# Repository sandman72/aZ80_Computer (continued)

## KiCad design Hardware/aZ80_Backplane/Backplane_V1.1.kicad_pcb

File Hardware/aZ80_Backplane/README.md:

# aZ80 Bus-Platine

Die Bus-Platine bildet das Rückgrat unseres Computers. Sie verbindet die einzelnen Karten des aZ80 miteinander.

Die sieben Slots sind alle gleich belegt und leiten den Adress- und Datenbus sowie die Kontrollsignale und die Versorgungsspannung weiter an die verschiedenen Karten.

Die LED D2 zeigt an, dass eine Versorgungsspannung anliegt.

Der Taster SW1 erlaubt das Zurücksetzen und Neustarten des Computers, der sogenannte RESET. Dies ist hilfreich, wenn der aZ80 mal nicht mehr reagieren sollte.

Im Kurs zeigen wir euch, wie man diese Platinen am besten zusammen lötet.

#### Externe Anschlüsse:

 - J1 - Steckleiste für Serielles Interfaces (FTDI Belegung)
 - J2 - Buchse für die externe 5V Versorgungsspannung (Barrel-Jack, Mitte +5V)
 - J3 - +5V Messpunkt für die Versorgungsspannung.
 - J4 - Masse Messpunkt für die Versorgungsspannung.

#### Steckbrücken (Jumper):

 - JP1 - Steuerleitung RTS des FTDI USB Seriell Wandlers mit Leitung USR1 verbinden
 - JP2 - Stromversorgung per FTDI USB Seriell Wandler erlauben

Unser aZ80 Computer benötigt eine +5V Versorgungsspannung von etwa 300mA, was einen Betrieb über den FTDI USB Seriell Wandler erlaubt, wenn nicht noch weitere Zusatzkarten (Video, Audio usw.) eingesteckt sind. In diesem Falle sollte man über die Buchse J2 ein USB-Netzteil anschließen.

Der BUS ist größtenteils kompatibel mit dem sogenannten RC40 System (Retro Computer 40), dass auch im RC2014 Computer benutzt wird. Hierzu gibt es diverse Erweiterungsplatinen, die auch zum großen Teil mit dem aZ80 kompatibel sind.

#### Pin-Belegung der aZ80 Busses:

|   Pin   |  Signal  |
|--------:|:---------|
|  1 - 16 | A15-A0 	Adress-Bus | 
|      17 | GND		Masse |
|      18 | VCC +5V	Versorgungsspannung |
|      19 | M1		Steuerungssignal |
|      20 | RESET		Zurücksetzen des Systems |
|      21 | CLOCK		Taktsignal 3,68MHz |
|      22 | INT		Interrupt, Unterbrechungsanforderung |
|      23 | MREQ		Memory Request, Speicheranfrage |
|      24 | WR		Write, Daten schreiben |
|      25 | RD		Read, Daten lesen |
|      26 | IORQ		I/O Request, I/O-Anfrage |
| 27 - 34 | D0-D7		Daten-Bus |
|      35 | TX		Serielle Daten Senden |
|      36 | RX		Serielle Daten Empfangen |
| 37 - 40 | USR1-USR4	Benutzerdefinierte Signale |  

Der Adress- und Daten-Bus ermöglicht dem Prozessor/CPU mit den einzelnen Karten Daten auszutauschen. Dabei enthält der Adress-Bus, wenn man so will, die Adresse eines Postfachs in das man was reinlegen oder rausholen möchte. Der Daten-Bus enthält die Information die dort gelesen wurde oder abgelegt werden soll.

Mit den Steuersignale (RD, WR, MREQ, IORQ, M1) legt der Prozessor fest, wie und von wo etwas gelesen oder geschrieben werden soll.   

#### Benutzerdefinierte Signale USR1-USR4:

Die vier USR1-USR4 Pins kann man selber nach Bedarf belegen. Die Serielle Karte kann z.B. über die Steuerleitung USR1 mit dem FTDI Seriell Wandler verbunden werden, was eine Flusssteuerung der Daten erlaubt. Dies ist nötig, wenn unser aZ80 lange BASIC Programme empfangen und nichts verloren gehen soll.

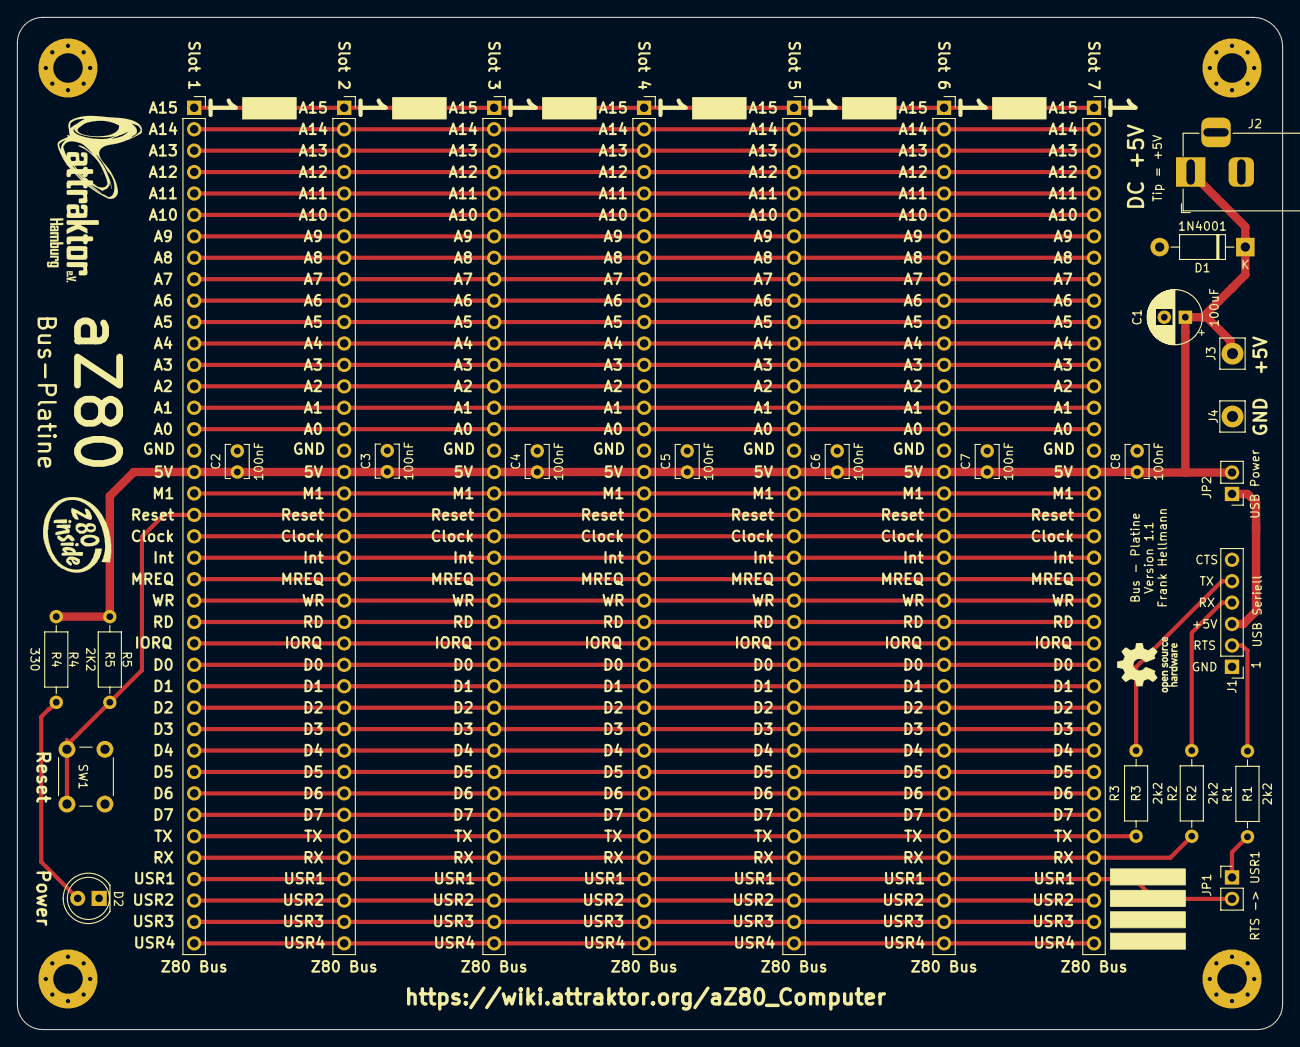
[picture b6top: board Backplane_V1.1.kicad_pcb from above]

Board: 2 copper layers, 150.0 x 120.0 mm, 33 parts (0 on the bottom side), 46 nets.

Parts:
C1: 100uF; CP_Radial_D6.3mm_P2.50mm
C2, C3, C4, C5, C6, C7, C8: 100nF; C_Disc_D3.8mm_W2.6mm_P2.50mm
D1: 1N4001; D_DO-41_SOD81_P10.16mm_Horizontal
D2: Power; LED_D5.0mm
Hole1, Hole2, Hole3, Hole4: MountingHole_3.5mm_Pad_Via
J1: USB Seriell; PinHeader_1x06_P2.54mm_Vertical
J2: DC +5V; BarrelJack_Horizontal
J3: +5V Hook; Pin_D1.3mm_L10.0mm_W3.5mm_Flat
J4: GND Hook; Pin_D1.3mm_L10.0mm_W3.5mm_Flat
JP1: RTS -> USR1; PinHeader_1x02_P2.54mm_Vertical
JP2: 5V USB; PinHeader_1x02_P2.54mm_Vertical
R1, R2, R3: 2k2; R_Axial_DIN0207_L6.3mm_D2.5mm_P10.16mm_Horizontal
R4: 330; R_Axial_DIN0207_L6.3mm_D2.5mm_P10.16mm_Horizontal
R5: 2K2; R_Axial_DIN0207_L6.3mm_D2.5mm_P10.16mm_Horizontal
SW1: Reset; SW_PUSH_6mm
Slot 1, Slot 2, Slot 3, Slot 4, Slot 5, Slot 6, Slot 7: Z80 Bus; PinSocket_1x40_P2.54mm_Vertical

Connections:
5V: C1.1, C2.1, C3.1, C4.1, C5.1, C6.1, C7.1, C8.1, D1.1, J2.1, J3.1, JP2.2, R4.1, R5.2, Slot 1.18, Slot 2.18, Slot 3.18, Slot 4.18, Slot 5.18, Slot 6.18, Slot 7.18
/A0: Slot 1.16, Slot 2.16, Slot 3.16, Slot 4.16, Slot 5.16, Slot 6.16, Slot 7.16
/A1: Slot 1.15, Slot 2.15, Slot 3.15, Slot 4.15, Slot 5.15, Slot 6.15, Slot 7.15
/A2: Slot 1.14, Slot 2.14, Slot 3.14, Slot 4.14, Slot 5.14, Slot 6.14, Slot 7.14
/A3: Slot 1.13, Slot 2.13, Slot 3.13, Slot 4.13, Slot 5.13, Slot 6.13, Slot 7.13
/A4: Slot 1.12, Slot 2.12, Slot 3.12, Slot 4.12, Slot 5.12, Slot 6.12, Slot 7.12
/A5: Slot 1.11, Slot 2.11, Slot 3.11, Slot 4.11, Slot 5.11, Slot 6.11, Slot 7.11
/A6: Slot 1.10, Slot 2.10, Slot 3.10, Slot 4.10, Slot 5.10, Slot 6.10, Slot 7.10
/A7: Slot 1.9, Slot 2.9, Slot 3.9, Slot 4.9, Slot 5.9, Slot 6.9, Slot 7.9
/A8: Slot 1.8, Slot 2.8, Slot 3.8, Slot 4.8, Slot 5.8, Slot 6.8, Slot 7.8
/A9: Slot 1.7, Slot 2.7, Slot 3.7, Slot 4.7, Slot 5.7, Slot 6.7, Slot 7.7
/A10: Slot 1.6, Slot 2.6, Slot 3.6, Slot 4.6, Slot 5.6, Slot 6.6, Slot 7.6
/A11: Slot 1.5, Slot 2.5, Slot 3.5, Slot 4.5, Slot 5.5, Slot 6.5, Slot 7.5
/A12: Slot 1.4, Slot 2.4, Slot 3.4, Slot 4.4, Slot 5.4, Slot 6.4, Slot 7.4
/A13: Slot 1.3, Slot 2.3, Slot 3.3, Slot 4.3, Slot 5.3, Slot 6.3, Slot 7.3
/A14: Slot 1.2, Slot 2.2, Slot 3.2, Slot 4.2, Slot 5.2, Slot 6.2, Slot 7.2
/A15: Slot 1.1, Slot 2.1, Slot 3.1, Slot 4.1, Slot 5.1, Slot 6.1, Slot 7.1
/CLK: Slot 1.21, Slot 2.21, Slot 3.21, Slot 4.21, Slot 5.21, Slot 6.21, Slot 7.21
/D0: Slot 1.27, Slot 2.27, Slot 3.27, Slot 4.27, Slot 5.27, Slot 6.27, Slot 7.27
/D1: Slot 1.28, Slot 2.28, Slot 3.28, Slot 4.28, Slot 5.28, Slot 6.28, Slot 7.28
/D2: Slot 1.29, Slot 2.29, Slot 3.29, Slot 4.29, Slot 5.29, Slot 6.29, Slot 7.29
/D3: Slot 1.30, Slot 2.30, Slot 3.30, Slot 4.30, Slot 5.30, Slot 6.30, Slot 7.30
/D4: Slot 1.31, Slot 2.31, Slot 3.31, Slot 4.31, Slot 5.31, Slot 6.31, Slot 7.31
/D5: Slot 1.32, Slot 2.32, Slot 3.32, Slot 4.32, Slot 5.32, Slot 6.32, Slot 7.32
/D6: Slot 1.33, Slot 2.33, Slot 3.33, Slot 4.33, Slot 5.33, Slot 6.33, Slot 7.33
/D7: Slot 1.34, Slot 2.34, Slot 3.34, Slot 4.34, Slot 5.34, Slot 6.34, Slot 7.34
/INT: Slot 1.22, Slot 2.22, Slot 3.22, Slot 4.22, Slot 5.22, Slot 6.22, Slot 7.22
/IORQ: Slot 1.26, Slot 2.26, Slot 3.26, Slot 4.26, Slot 5.26, Slot 6.26, Slot 7.26
/M1: Slot 1.19, Slot 2.19, Slot 3.19, Slot 4.19, Slot 5.19, Slot 6.19, Slot 7.19
/MREQ: Slot 1.23, Slot 2.23, Slot 3.23, Slot 4.23, Slot 5.23, Slot 6.23, Slot 7.23
/RD: Slot 1.25, Slot 2.25, Slot 3.25, Slot 4.25, Slot 5.25, Slot 6.25, Slot 7.25
/WR: Slot 1.24, Slot 2.24, Slot 3.24, Slot 4.24, Slot 5.24, Slot 6.24, Slot 7.24
GND: C1.2, C2.2, C3.2, C4.2, C5.2, C6.2, C7.2, C8.2, D1.2, D2.1, J1.1, J2.2, J4.1, SW1.2, Slot 1.17, Slot 2.17, Slot 3.17, Slot 4.17, Slot 5.17, Slot 6.17, Slot 7.17
unnamed: D2.2, R4.2
unnamed: J1.2, R1.2
unnamed: J1.3, JP2.1
unnamed: J1.4, R2.2
unnamed: J1.5, R3.2
unnamed: JP1.1, R1.1
RX: R2.1, Slot 1.36, Slot 2.36, Slot 3.36, Slot 4.36, Slot 5.36, Slot 6.36, Slot 7.36
Reset: R5.1, SW1.1, Slot 1.20, Slot 2.20, Slot 3.20, Slot 4.20, Slot 5.20, Slot 6.20, Slot 7.20
TX: R3.1, Slot 1.35, Slot 2.35, Slot 3.35, Slot 4.35, Slot 5.35, Slot 6.35, Slot 7.35
USR1: JP1.2, Slot 1.37, Slot 2.37, Slot 3.37, Slot 4.37, Slot 5.37, Slot 6.37, Slot 7.37
USR2: Slot 1.38, Slot 2.38, Slot 3.38, Slot 4.38, Slot 5.38, Slot 6.38, Slot 7.38
USR3: Slot 1.39, Slot 2.39, Slot 3.39, Slot 4.39, Slot 5.39, Slot 6.39, Slot 7.39
USR4: Slot 1.40, Slot 2.40, Slot 3.40, Slot 4.40, Slot 5.40, Slot 6.40, Slot 7.40

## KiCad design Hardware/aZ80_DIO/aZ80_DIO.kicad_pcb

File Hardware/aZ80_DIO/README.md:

# aZ80 Digital I/O Platine

Die DIO (Digital I/O) Platine stellt über Taster, Joystick Anschluss und LEDs eine Verbindung zur Aussenwelt her.

#### Port Auswahl

Über den Jumperblock JP1 kann die Adresse (Port) eingestellt werden, auf den die DIO Platine reagieren soll. 
Normalerweise ist dort O0 und I0 gesteckt, was bedeutet, dass die DIO Platine auf Addresse 0 beim Lesen und Schreiben reagiert.
Damit können auch mehrere Karten in einem aZ80 System genutzt werden, wenn alle Karten unterschiedliche Addressen bekommen.

#### LEDs

Die LEDs können über die eingestellte Addresse mit einem I/O Write eingeschaltet werden. 

```
Basic:   OUT 0, 170             schaltet jede zweite LED an Port 0 an.

ASM:     LD      A,%10101010
         OUT     IOPORT,A       schaltet jede zweite LED an Port 0 an.
```

#### Taster & Joystick

Die Taster und der Joystick können über die eingestellte Addresse mit einem I/O Read ausgelesen werden.

```
Basic:   A$=INP(0)     liest den Status der Taster in A$ ein

ASM:     IN A,(0)      liest den Status der Taster in Register A
```

#### Basic Beispiel um LED mit Button einzuschalten

```
10 OUT 0,INP(0)
20 GOTO 10
```

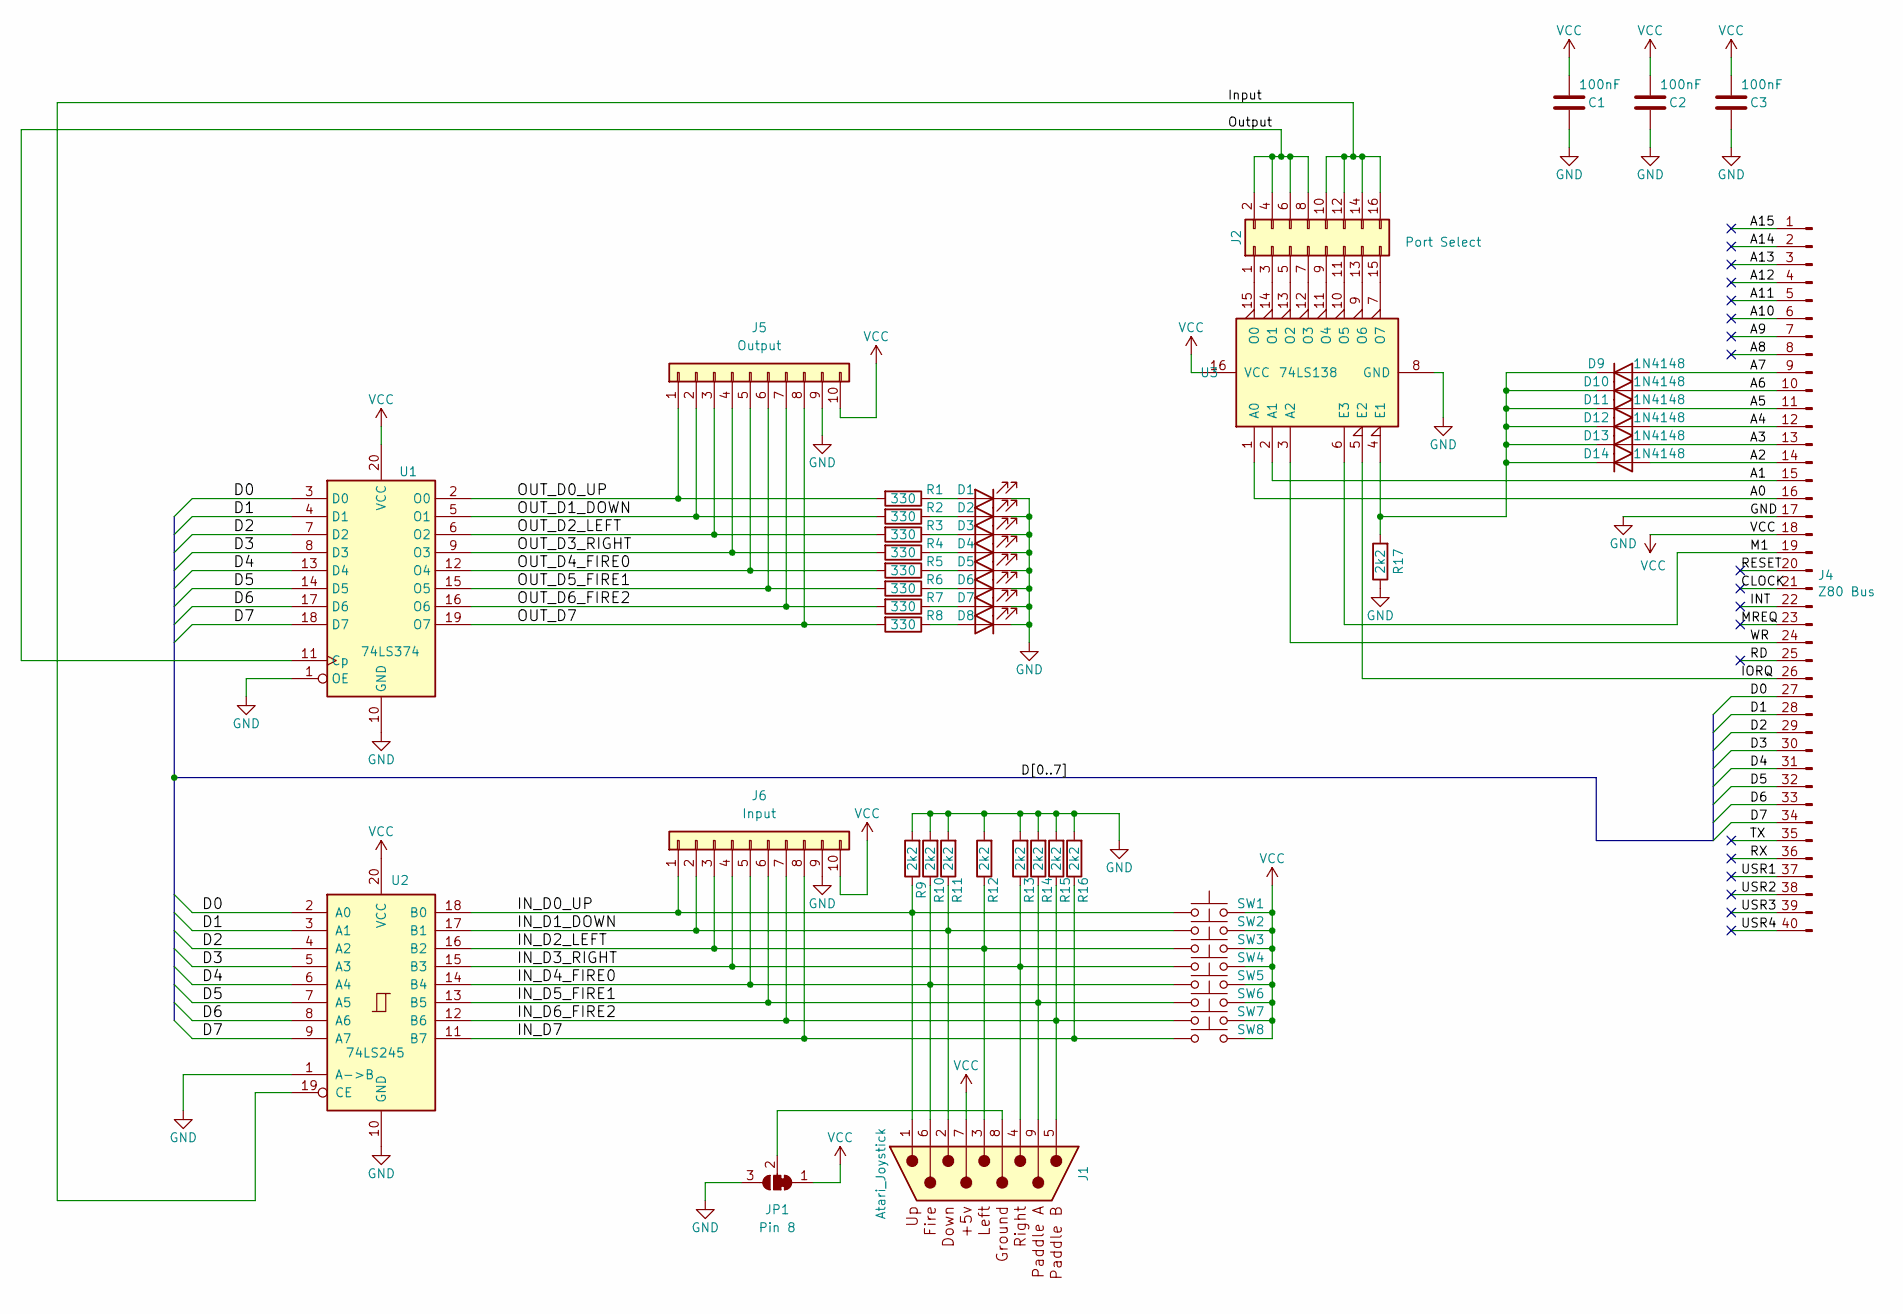
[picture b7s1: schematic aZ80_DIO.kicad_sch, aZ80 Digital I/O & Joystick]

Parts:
C1, C2, C3: 100nF; C_Disc_D3.8mm_W2.6mm_P2.50mm
D1, D2, D3, D4, D5, D6, D7, D8: LED_Small; LED_D5.0mm
D9, D10, D11, D12, D13, D14: 1N4148; D_DO-35_SOD27_P7.62mm_Horizontal
J1: Atari_Joystick; DSUB-9_Male_Horizontal_P2.77x2.84mm_EdgePinOffset7.70mm_Hou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
J2: Port Select; PinHeader_2x08_P2.54mm_Vertical
J4: Z80 Bus; PinHeader_1x40_P2.54mm_Horizontal
J5: Output; PinHeader_1x10_P2.54mm_Vertical
J6: Input; PinHeader_1x10_P2.54mm_Vertical
JP1: Pin 8; SolderJumper-3_P1.3mm_Bridged2Bar12_RoundedPad1.0x1.5mm
R1, R2, R3, R4, R5, R6, R7, R8: 330; R_Axial_DIN0207_L6.3mm_D2.5mm_P10.16mm_Horizontal
R9, R10, R11, R12, R13, R14, R15, R16, R17: 2k2; R_Axial_DIN0207_L6.3mm_D2.5mm_P10.16mm_Horizontal
SW1, SW2, SW3, SW4, SW5, SW6, SW7, SW8: SW_Push; SW_PUSH_6mm
U1: 74LS374; DIP-20_W7.62mm_LongPads
U2: 74LS245; DIP-20_W7.62mm_LongPads
U3: 74LS138; DIP-16_W7.62mm_LongPads

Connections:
/A0: J4.16, U3.1 (A0)
/A1: J4.15, U3.2 (A1)
/A2: D14.2 (A), J4.14
/A3: D13.2 (A), J4.13
/A4: D12.2 (A), J4.12
/A5: D11.2 (A), J4.11
/A6: D10.2 (A), J4.10
/A7: D9.2 (A), J4.9
/A8: J4.8
/A9: J4.7
/A10: J4.6
/A11: J4.5
/A12: J4.4
/A13: J4.3
/A14: J4.2
/A15: J4.1
/CLOCK: J4.21
/D0: J4.27, U1.3 (D0), U2.2 (A0)
/D1: J4.28, U1.4 (D1), U2.3 (A1)
/D2: J4.29, U1.7 (D2), U2.4 (A2)
/D3: J4.30, U1.8 (D3), U2.5 (A3)
/D4: J4.31, U1.13 (D4), U2.6 (A4)
/D5: J4.32, U1.14 (D5), U2.7 (A5)
/D6: J4.33, U1.17 (D6), U2.8 (A6)
/D7: J4.34, U1.18 (D7), U2.9 (A7)
/INT: J4.22
/IN_D0_UP: J1.1, J6.1, R9.1, SW1.1, U2.18 (B0)
/IN_D1_DOWN: J1.2, J6.2, R11.1, SW2.1, U2.17 (B1)
/IN_D2_LEFT: J1.3, J6.3, R12.1, SW3.1, U2.16 (B2)
/IN_D3_RIGHT: J1.4, J6.4, R13.1, SW4.1, U2.15 (B3)
/IN_D4_FIRE0: J1.6, J6.5, R10.1, SW5.1, U2.14 (B4)
/IN_D5_FIRE1: J1.9, J6.6, R14.1, SW6.1, U2.13 (B5)
/IN_D6_FIRE2: J1.5, J6.7, R15.1, SW7.1, U2.12 (B6)
/IN_D7: J6.8, R16.1, SW8.1, U2.11 (B7)
/IORQ: J4.26, U3.5 (E2)
/Input: J2.10, J2.12, J2.14, J2.16, U2.19 (CE)
/M1: J4.19, U3.6 (E3)
/MREQ: J4.23
/OUT_D0_UP: J5.1, R1.2, U1.2 (O0)
/OUT_D1_DOWN: J5.2, R2.2, U1.5 (O1)
/OUT_D2_LEFT: J5.3, R3.2, U1.6 (O2)
/OUT_D3_RIGHT: J5.4, R4.2, U1.9 (O3)
/OUT_D4_FIRE0: J5.5, R5.2, U1.12 (O4)
/OUT_D5_FIRE1: J5.6, R6.2, U1.15 (O5)
/OUT_D6_FIRE2: J5.7, R7.2, U1.16 (O6)
/OUT_D7: J5.8, R8.2, U1.19 (O7)
/Output: J2.2, J2.4, J2.6, J2.8, U1.11 (Cp)
/RD: J4.25
/RESET: J4.20
/RX: J4.36
/TX: J4.35
/USR1: J4.37
/USR2: J4.38
/USR3: J4.39
/USR4: J4.40
/WR: J4.24, U3.3 (A2)
GND: C1.2, C2.2, C3.2, D1.1 (K), D2.1 (K), D3.1 (K), D4.1 (K), D5.1 (K), D6.1 (K), D7.1 (K), D8.1 (K), J4.17, J5.9, J6.9, JP1.3 (B), R9.2, R10.2, R11.2, R12.2, R13.2, R14.2, R15.2, R16.2, R17.1, U1.1 (OE), U1.10 (GND), U2.1 (A->B), U2.10 (GND), U3.8 (GND)
unnamed: D1.2 (A), R1.1
unnamed: D2.2 (A), R2.1
unnamed: D3.2 (A), R3.1
unnamed: D4.2 (A), R4.1
unnamed: D5.2 (A), R5.1
unnamed: D6.2 (A), R6.1
unnamed: D7.2 (A), R7.1
unnamed: D8.2 (A), R8.1
unnamed: D9.1 (K), D10.1 (K), D11.1 (K), D12.1 (K), D13.1 (K), D14.1 (K), R17.2, U3.4 (E1)
unnamed: J2.1, U3.15 (O0)
unnamed: J2.3, U3.14 (O1)
unnamed: J2.5, U3.13 (O2)
unnamed: J2.7, U3.12 (O3)
unnamed: J2.9, U3.11 (O4)
unnamed: J2.11, U3.10 (O5)
unnamed: J2.13, U3.9 (O6)
unnamed: J2.15, U3.7 (O7)
unnamed: J1.8, JP1.2 (C)
VCC: C1.1, C2.1, C3.1, J1.7, J4.18, J5.10, J6.10, JP1.1 (A), SW1.2, SW2.2, SW3.2, SW4.2, SW5.2, SW6.2, SW7.2, SW8.2, U1.20 (VCC), U2.20 (VCC), U3.16 (VCC)

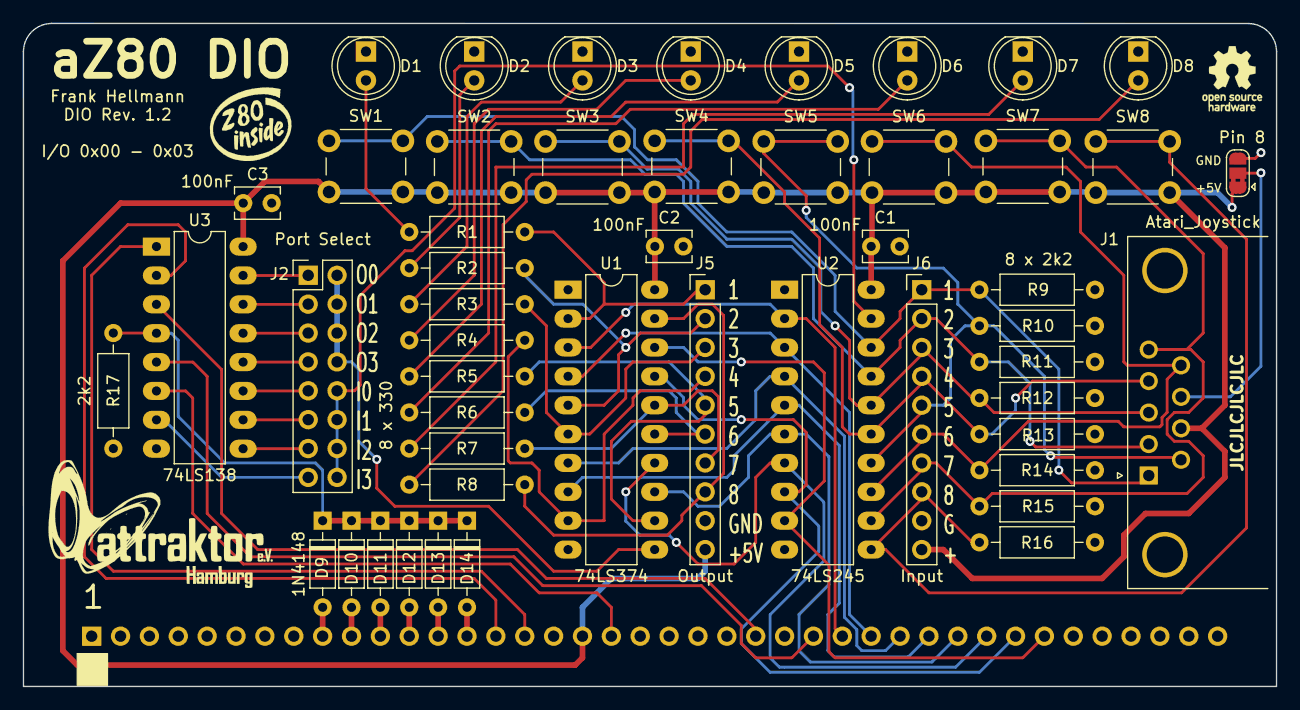
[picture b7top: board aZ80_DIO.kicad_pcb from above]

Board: 2 copper layers, 110.3 x 58.3 mm, 51 parts (1 on the bottom side), 57 nets.

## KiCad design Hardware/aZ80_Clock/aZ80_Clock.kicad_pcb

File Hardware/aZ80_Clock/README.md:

# aZ80 Taktgenerator Platine

Die Taktgenerator Platine gibt den Takt des aZ80 Retro Computers vor und synchronisiert alle Karten.

Es gibt zwei Modis die mit dem Jumper JP1 umgestellt werden können:

 - 1 - Volle Geschwindigkeit mit 3.6864 MHz
 - 2 - Langsame Geschwindigkeit mit 4-20Hz

Im Normalfall läuft das aZ80 Retro System mit vollem 3.6864Mhz Takt, welcher auch die serielle Baudrate von 57.600 Baud vorgibt.

Bei der langsamen Geschwindigkeit kann man dem System besser "auf den Zahn fühlen", z.B. mit einem Logic Analyser oder der Digital I/O Karte, hat aber keine serielle Verbindung mehr.
Das Poti RV1 erlaubt das Einstellen der Geschwindigkeit im Rahmen von ca. 4 bis 20 Herz.

Die Status LEDs zeigen an, was auf dem aZ80 Bus so los ist:

 - RD - Es wird auf dem Bus etwas gelesen
 - WR - Es wird auf dem Bus etwas geschrieben
 - INT - Es ist ein Interrupt ausgelöst worden
 - CLK - Hier wird der aktuelle Takt als Blinken angezeigt

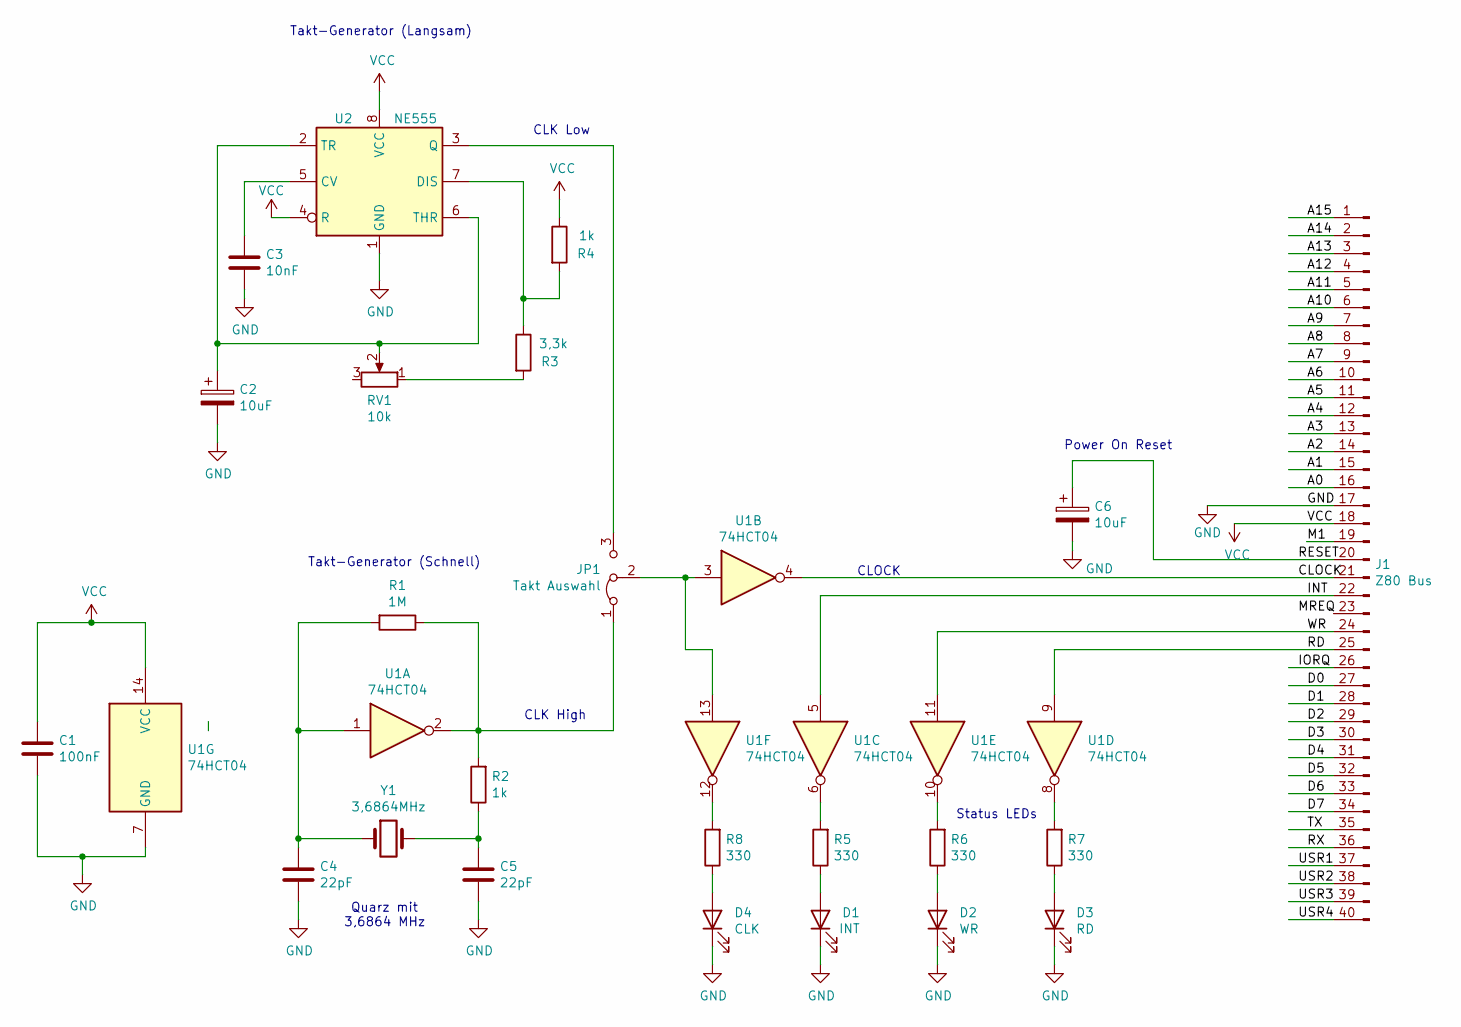
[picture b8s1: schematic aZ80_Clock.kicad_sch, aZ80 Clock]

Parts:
C1: 100nF; C_Disc_D3.8mm_W2.6mm_P2.50mm
C2, C6: 10uF; CP_Radial_D5.0mm_P2.50mm
C3: 10nF; C_Disc_D3.8mm_W2.6mm_P2.50mm
C4, C5: 22pF; C_Disc_D3.8mm_W2.6mm_P2.50mm
D1: INT; LED_D5.0mm
D2: WR; LED_D5.0mm
D3: RD; LED_D5.0mm
D4: CLK; LED_D5.0mm
J1: Z80 Bus; PinHeader_1x40_P2.54mm_Horizontal
JP1: Takt Auswahl; PinHeader_1x03_P2.54mm_Vertical
R1: 1M; R_Axial_DIN0207_L6.3mm_D2.5mm_P10.16mm_Horizontal
R2, R4: 1k; R_Axial_DIN0207_L6.3mm_D2.5mm_P10.16mm_Horizontal
R3: 3,3k; R_Axial_DIN0207_L6.3mm_D2.5mm_P10.16mm_Horizontal
R5, R6, R7, R8: 330; R_Axial_DIN0207_L6.3mm_D2.5mm_P10.16mm_Horizontal
RV1: 10k; Potentiometer_Piher_PT-10-H01_Horizontal
U1: 74HCT04; DIP-14_W7.62mm_Socket_LongPads
U2: NE555; DIP-8_W7.62mm_Socket_LongPads
Y1: 3,6864MHz; Crystal_HC49-4H_Vertical

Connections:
/A0: J1.16
/A1: J1.15
/A2: J1.14
/A3: J1.13
/A4: J1.12
/A5: J1.11
/A6: J1.10
/A7: J1.9
/A8: J1.8
/A9: J1.7
/A10: J1.6
/A11: J1.5
/A12: J1.4
/A13: J1.3
/A14: J1.2
/A15: J1.1
/CLOCK: J1.21, U1.4
/D0: J1.27
/D1: J1.28
/D2: J1.29
/D3: J1.30
/D4: J1.31
/D5: J1.32
/D6: J1.33
/D7: J1.34
/INT: J1.22, U1.5
/IORQ: J1.26
/M1: J1.19
/RD: J1.25, U1.9
/RESET: C6.1, J1.20
/RX: J1.36
/TX: J1.35
/USR1: J1.37
/USR2: J1.38
/USR3: J1.39
/USR4: J1.40
/WR: J1.24, U1.11
GND: C1.2, C2.2, C3.2, C4.2, C5.2, C6.2, D1.1 (K), D2.1 (K), D3.1 (K), D4.1 (K), J1.17, U1.7 (GND), U2.1 (GND)
unnamed: C2.1, RV1.2, U2.2 (TR), U2.6 (THR)
unnamed: C3.1, U2.5 (CV)
unnamed: C4.1, R1.2, U1.1, Y1.1
unnamed: C5.1, R2.1, Y1.2
unnamed: D1.2 (A), R5.1
unnamed: D2.2 (A), R6.1
unnamed: D3.2 (A), R7.1
unnamed: D4.2 (A), R8.1
unnamed: JP1.1 (A), R1.1, R2.2, U1.2
unnamed: JP1.2 (C), U1.3, U1.13
unnamed: JP1.3 (B), U2.3 (Q)
unnamed: R3.1, R4.2, U2.7 (DIS)
unnamed: R3.2, RV1.1
unnamed: R5.2, U1.6
unnamed: R6.2, U1.10
unnamed: R7.2, U1.8
unnamed: R8.2, U1.12
VCC: C1.1, J1.18, R4.1, U1.14 (VCC), U2.4 (R), U2.8 (VCC)

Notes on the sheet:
CLK High
Takt-Generator (Schnell)
CLK Low
CLOCK
Power On Reset
Quarz mit 3,6864 MHz
Status LEDs
Takt-Generator (Langsam)

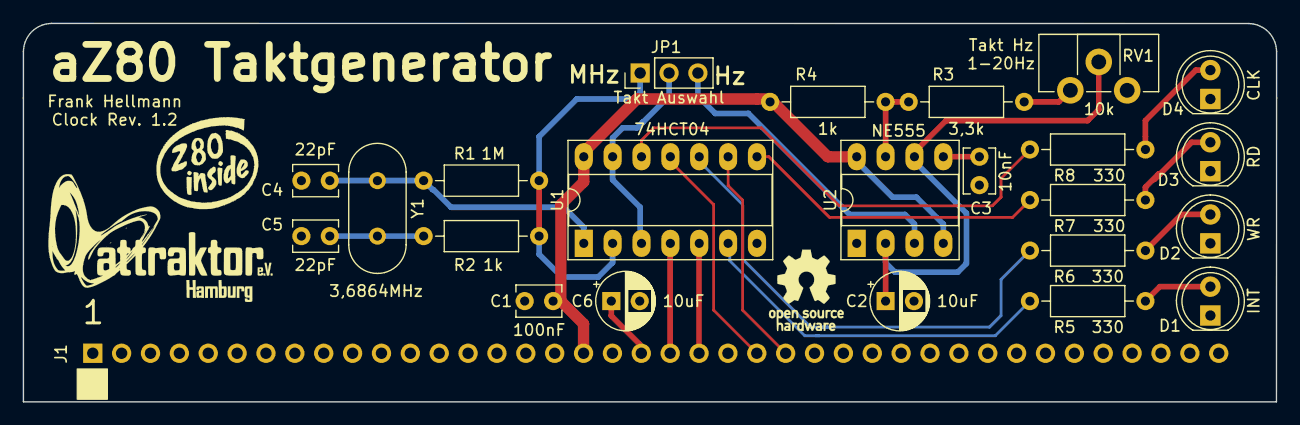
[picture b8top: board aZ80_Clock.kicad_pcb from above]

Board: 2 copper layers, 110.2 x 33.3 mm, 24 parts (1 on the bottom side), 24 nets.

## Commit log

2025-02-16 initial V1.0 upload
2025-02-17 Update Diag_ROM_1.0.z80 License
